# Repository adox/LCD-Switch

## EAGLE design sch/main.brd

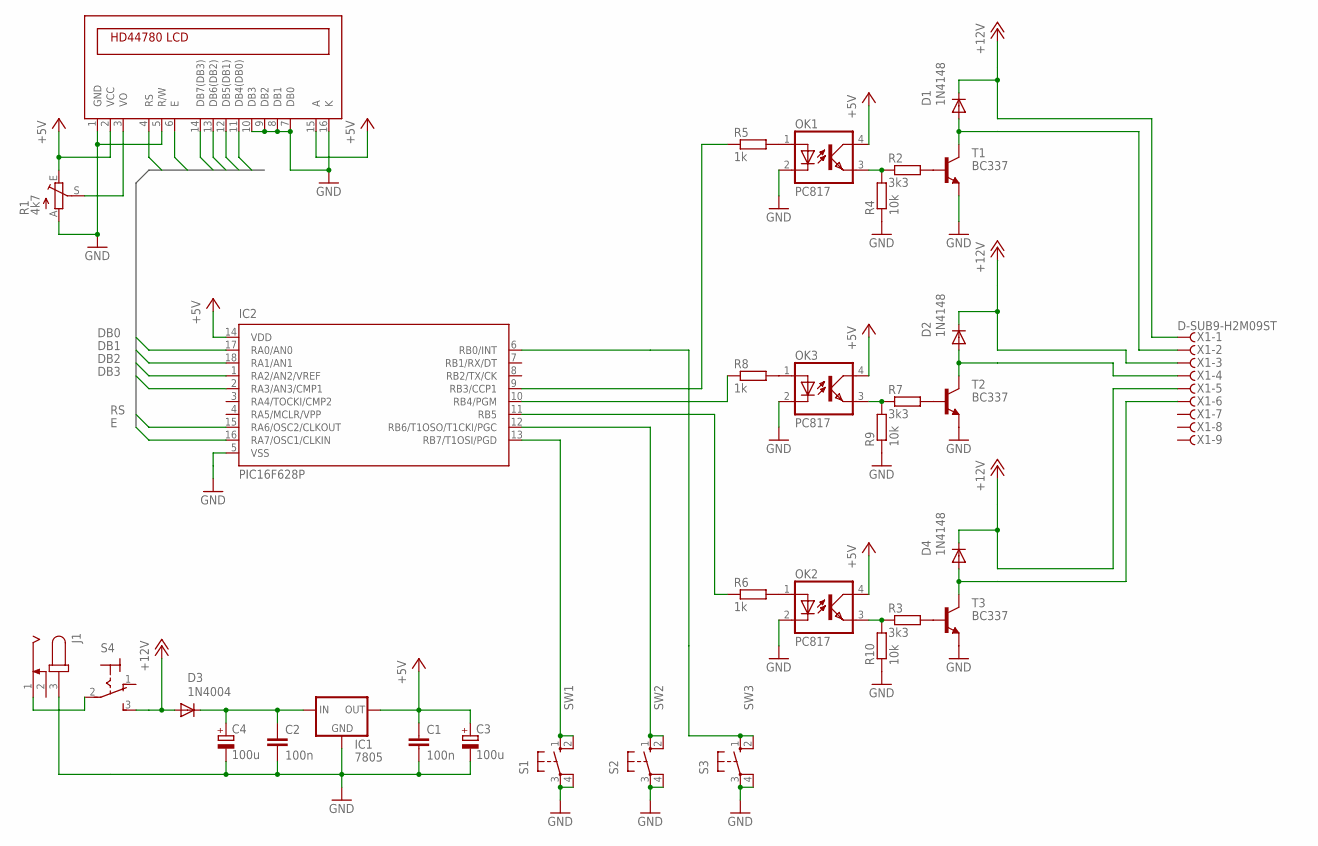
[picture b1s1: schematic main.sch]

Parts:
C1, C2: 100n; C025-025X050
C3, C4: 100u; E2,5-7
D1, D2, D4: 1N4148; DO35-7
D3: 1N4004; DO41-10
IC1: 7805; 78XXL
IC2: PIC16F628P; DIL18
J1: JACK-PLUG0; SPC4077
OK1, OK2, OK3: PC817; DIL04
R1: 4k7; CA6V
R2, R3, R7: 3k3; 0207/10
R4, R9, R10: 10k; 0207/10
R5, R6, R8: 1k; 0207/10
S1, S2, S3: 10-XX; B3F-10XX
S4: 320-916
T1, T2, T3: BC337; TO92-CBE
U1: YM1602G_LOWCON
X1: D-SUB9-H2M09ST; H2M09ST

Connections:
+5V: C1.1, C3.+, IC1.OUT, IC2.14 (VDD), OK1.4 (COL), OK2.4 (COL), OK3.4 (COL), R1.E, U1.2 (VCC), U1.15 (A)
+12V: D1.C, D2.C, D3.A, D4.C, S4.3 (S), X1.1, X1.3, X1.5
DB0: IC2.17 (RA0/AN0), U1.11 (DB4(DB0))
DB1: IC2.18 (RA1/AN1), U1.12 (DB5(DB1))
DB2: IC2.1 (RA2/AN2/VREF), U1.13 (DB6(DB2))
DB3: IC2.2 (RA3/AN3/CMP1), U1.14 (DB7(DB3))
E: IC2.16 (RA7/OSC1/CLKIN), U1.6 (E)
GND: C1.2, C2.2, C3.-, C4.-, IC1.GND, IC2.5 (VSS), J1.3, OK1.2 (C), OK2.2 (C), OK3.2 (C), R1.A, R4.1, R9.1, R10.1, S1.3, S1.4 (P1), S2.3, S2.4 (P1), S3.3, S3.4 (P1), T1.E, T2.E, T3.E, U1.1 (GND), U1.5 (R/W), U1.7 (DB0), U1.8 (DB1), U1.9 (DB2), U1.10 (DB3), U1.16 (K)
unnamed: R2.2, T1.B
unnamed: D1.A, T1.C, X1.2
unnamed: C2.1, C4.+, D3.C, IC1.IN
unnamed: OK2.1 (A), R6.2
unnamed: D2.A, T2.C, X1.4
unnamed: IC2.9 (RB3/CCP1), R5.1
unnamed: IC2.11 (RB5), R6.1
unnamed: R3.2, T3.B
unnamed: D4.A, T3.C, X1.6
unnamed: IC2.10 (RB4/PGM), R8.1
unnamed: R1.S, U1.3 (VO)
unnamed: J1.1, S4.2
unnamed: OK1.1 (A), R5.2
unnamed: OK1.3 (EMIT), R2.1, R4.2
unnamed: OK2.3 (EMIT), R3.1, R10.2
unnamed: OK3.1 (A), R8.2
unnamed: R7.2, T2.B
unnamed: OK3.3 (EMIT), R7.1, R9.2
RS: IC2.15 (RA6/OSC2/CLKOUT), U1.4 (RS)
SW1: IC2.13 (RB7/T1OSI/PGD), S1.1 (S), S1.2 (S1)
SW2: IC2.12 (RB6/T1OSO/T1CKI/PGC), S2.1 (S), S2.2 (S1)
SW3: IC2.6 (RB0/INT), S3.1 (S), S3.2 (S1)

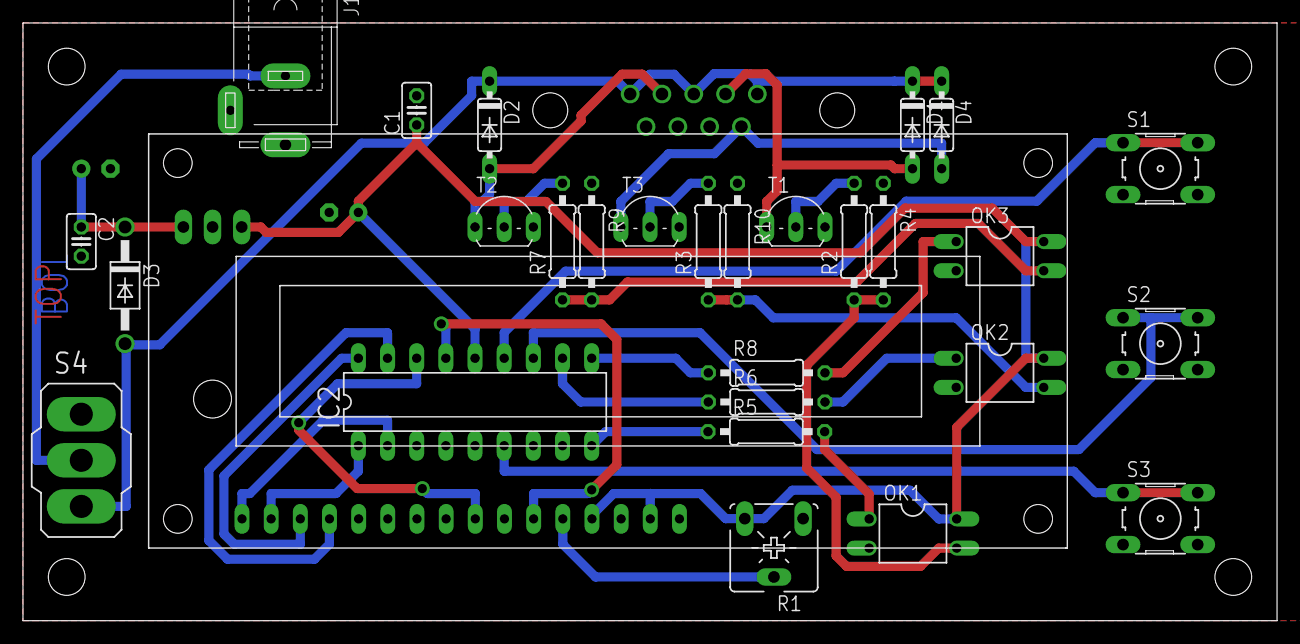
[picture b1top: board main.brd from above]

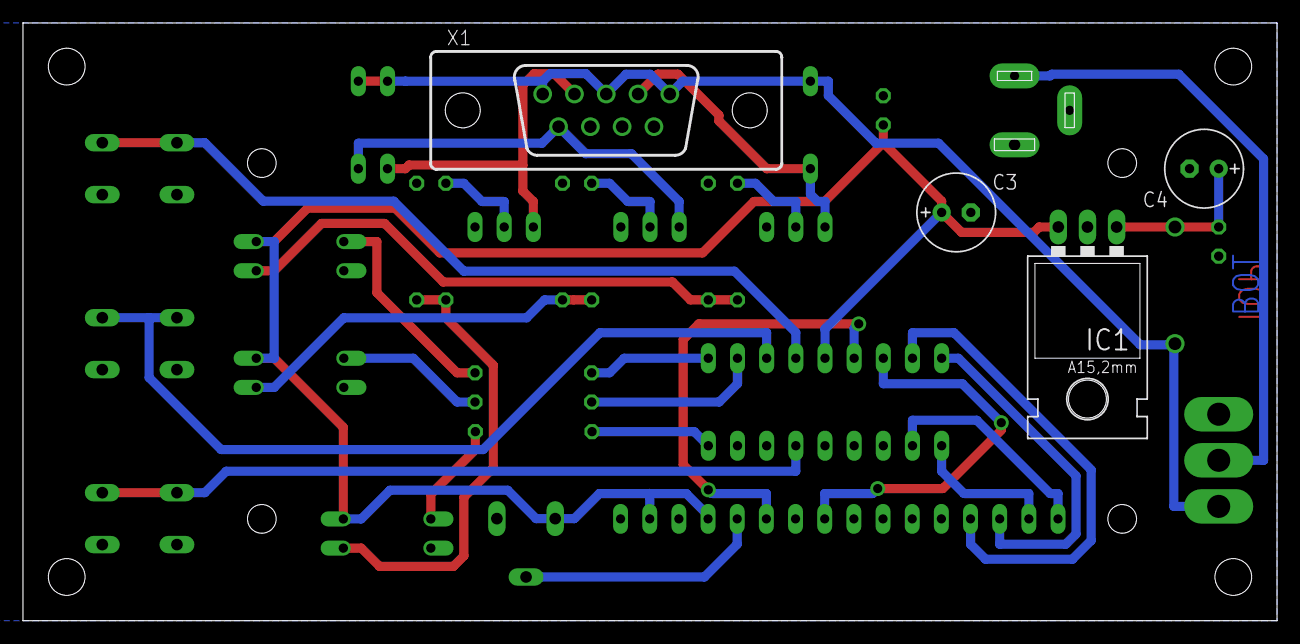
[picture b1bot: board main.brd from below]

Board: 2 copper layers, 109.2 x 52.1 mm, 33 parts (4 on the bottom side), 30 nets.

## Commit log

2012-07-03 Better routing
2012-07-03 Replaced relays with transistors
2012-07-04 First version for manufacturing
2012-07-11 Updated 3d model
2012-07-23 Removed short of GND and E
2012-07-26 Added firmware 0.1
2012-08-06 Several packages change, re-routed
2012-08-08 Added capacitor to power input
